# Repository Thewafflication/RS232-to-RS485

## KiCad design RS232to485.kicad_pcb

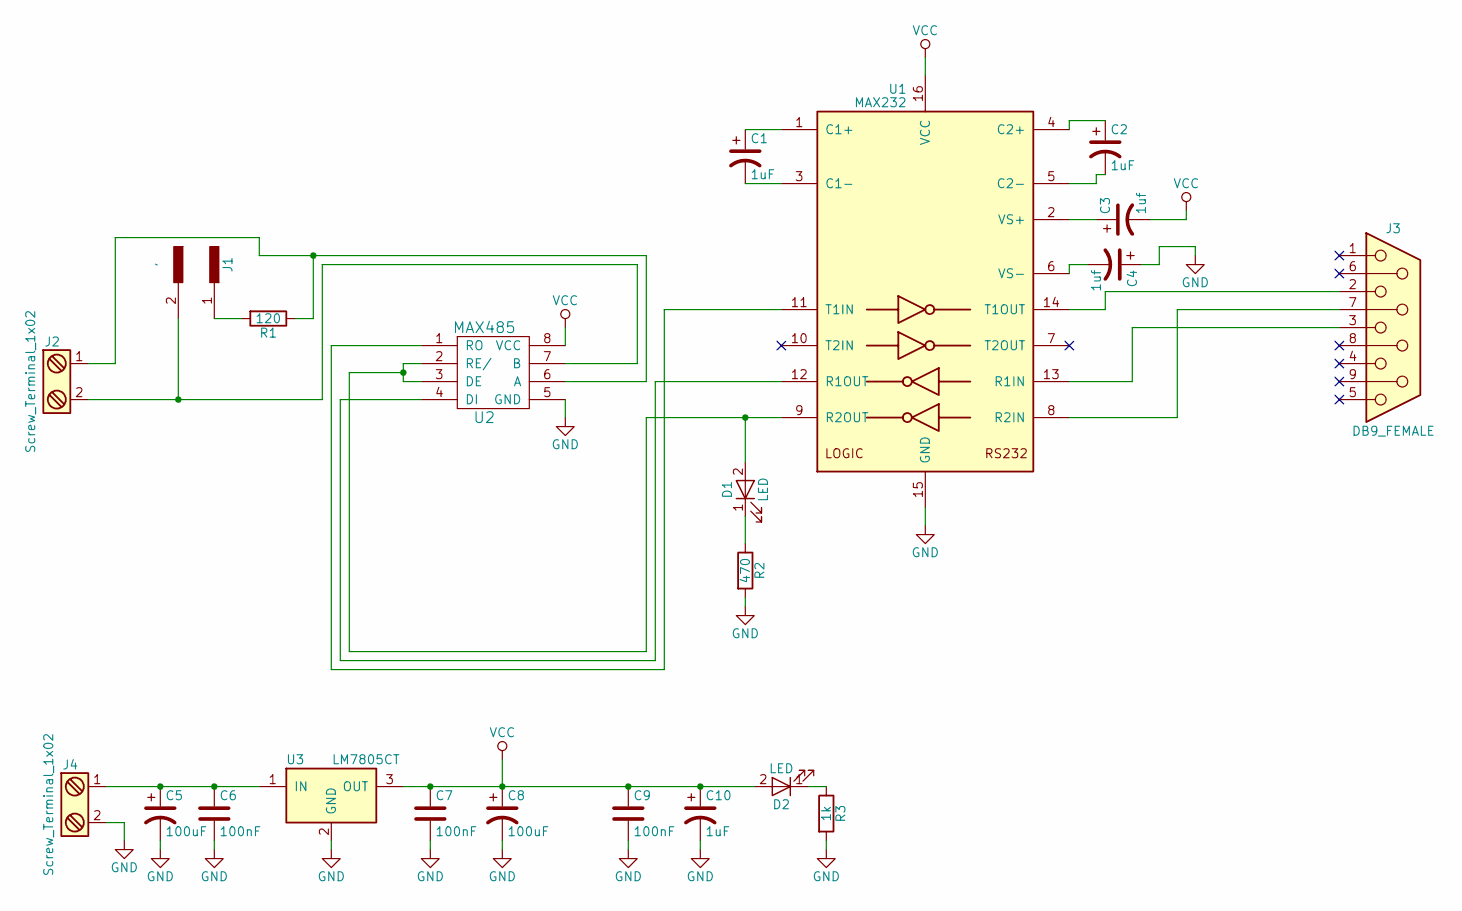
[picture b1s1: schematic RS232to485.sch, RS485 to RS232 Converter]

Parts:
C1, C2, C10: 1uF
C3, C4: 1uf
C5, C8: 100uF
C6, C7, C9: 100nF
D1, D2: LED
J1: '
J2, J4: Screw_Terminal_1x02
J3: DB9_FEMALE
R1: 120
R2: 470
R3: 1k
U1: MAX232
U2: MAX485
U3: LM7805CT; TO-220_Vertical

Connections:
GND: C4.1, C5.2, C6.2, C7.2, C8.2, C9.2, C10.2, J4.2, R2.2, R3.2, U1.15 (GND), U2.5 (GND), U3.2 (GND)
unnamed: C1.1, U1.1 (C1+)
unnamed: C1.2, U1.3 (C1-)
unnamed: C2.1, U1.4 (C2+)
unnamed: C2.2, U1.5 (C2-)
unnamed: C3.1, U1.2 (VS+)
unnamed: C4.2, U1.6 (VS-)
unnamed: C5.1, C6.1, J4.1, U3.1 (IN)
unnamed: D1.1 (K), R2.1
unnamed: D1.2 (A), U1.9 (R2OUT), U2.2 (RE/), U2.3 (DE)
unnamed: D2.1 (K), R3.1
unnamed: J1.1, R1.2
unnamed: J1.2, J2.2, U2.7 (B)
unnamed: J2.1, R1.1, U2.6 (A)
unnamed: J3.2, U1.14 (T1OUT)
unnamed: J3.3, U1.13 (R1IN)
unnamed: J3.7, U1.8 (R2IN)
unnamed: U1.11 (T1IN), U2.1 (RO)
unnamed: U1.12 (R1OUT), U2.4 (DI)
VCC: C3.2, C7.1, C8.1, C9.1, C10.1, D2.2 (A), U1.16 (VCC), U2.8 (VCC), U3.3 (OUT)

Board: 2 copper layers, 22 parts (0 on the bottom side), 20 nets, no tracks yet.
